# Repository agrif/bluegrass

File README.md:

This is an STM32 board (a la "Blue Pill") with built-in circuitry to charge
a single-cell lithium battery, over USB or DC input. It provides 5V and 3.3V
both at 1A, low standby current, battery fuel gauging, and supports charging
from a solar panel.

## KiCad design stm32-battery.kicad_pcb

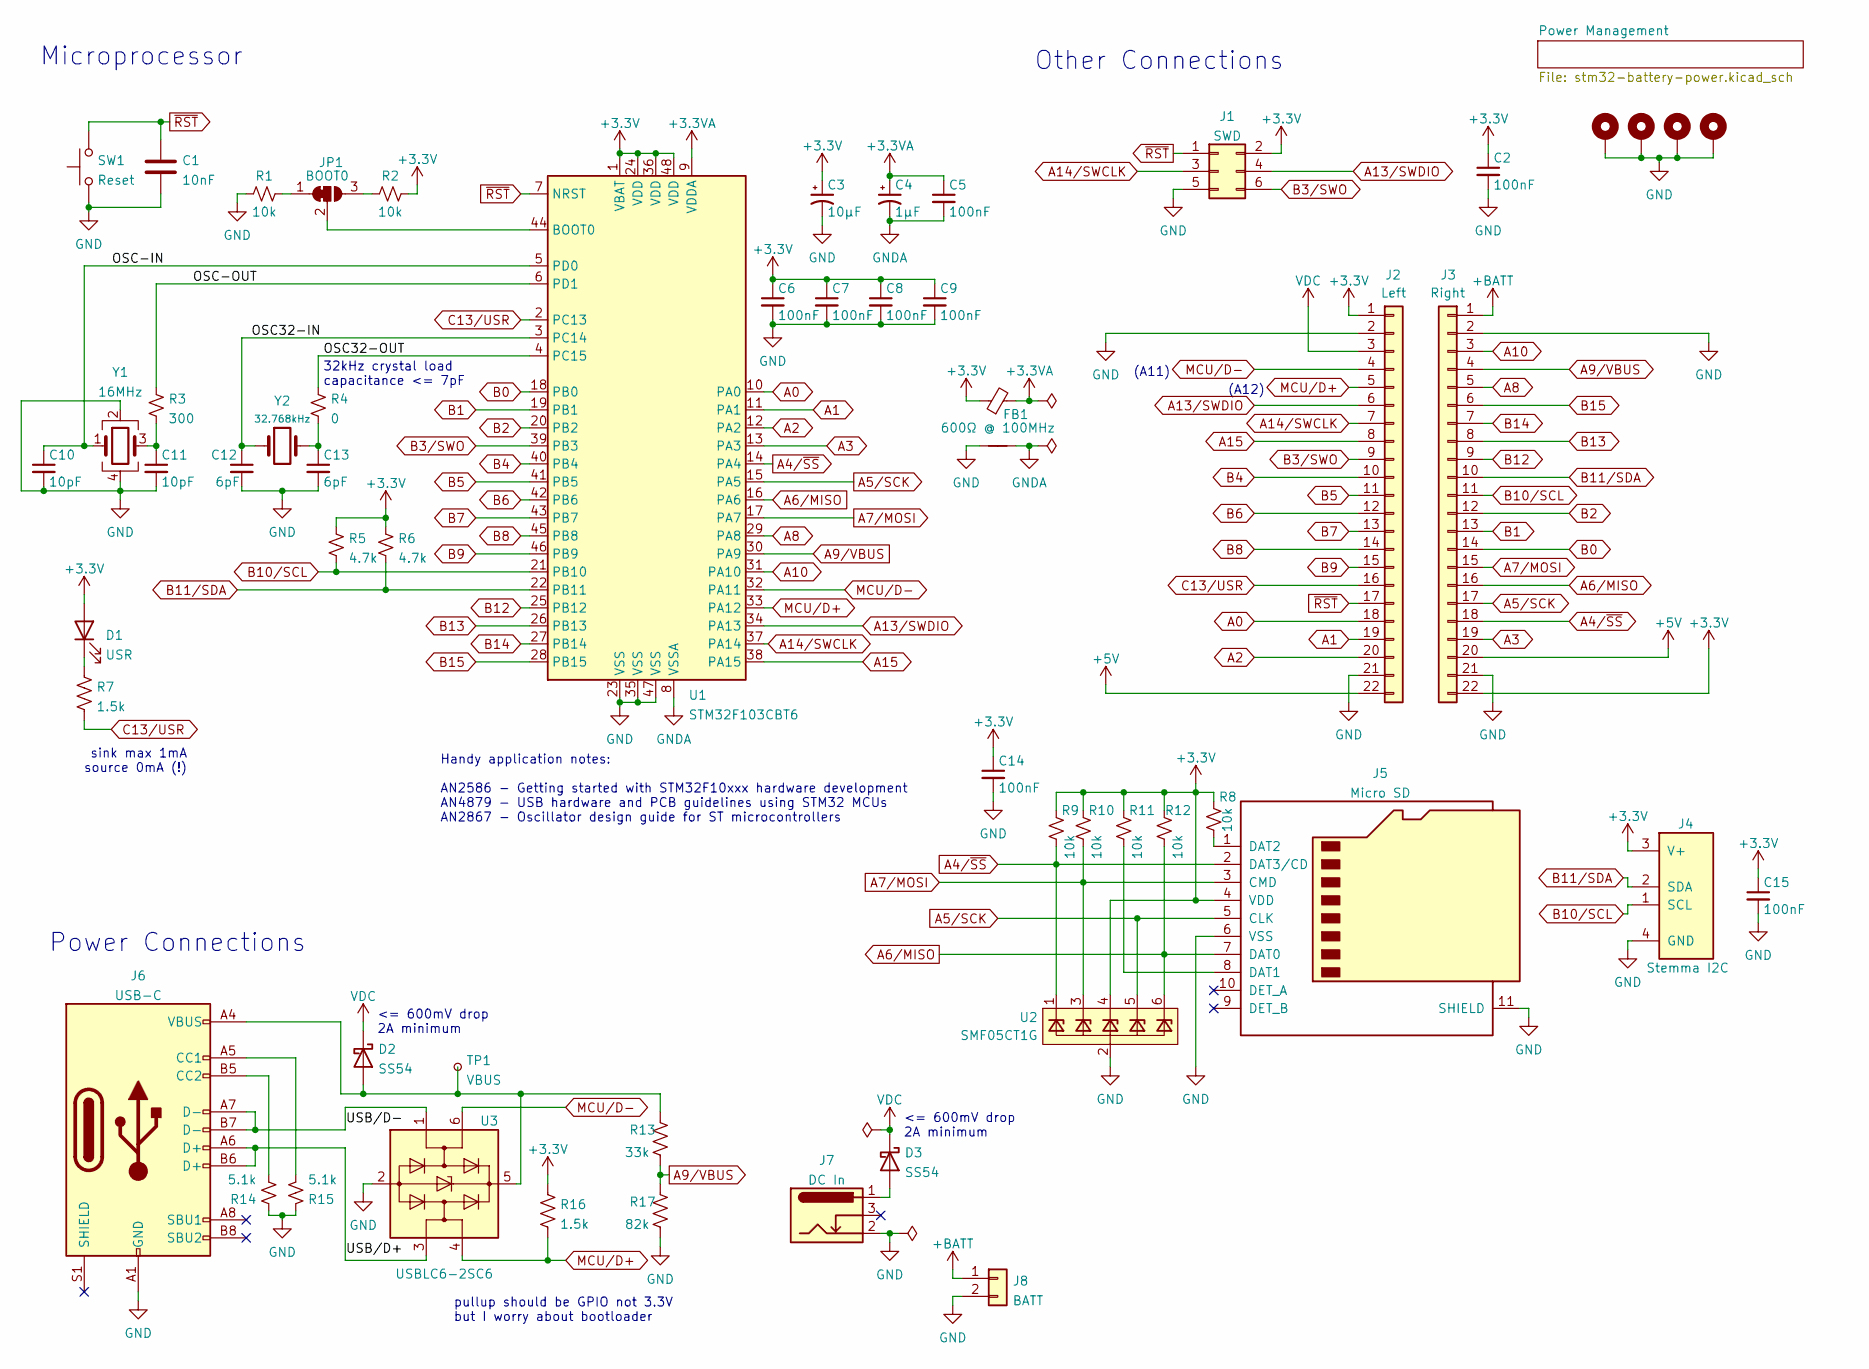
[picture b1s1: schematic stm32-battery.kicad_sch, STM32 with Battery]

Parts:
C1: 10nF; C_0805_2012Metric; LCSC Part # C1710
C2, C5, C6, C7, C8, C9, C14, C15: 100nF; C_0603_1608Metric; LCSC Part # C14663
C3: 10µF; C_0805_2012Metric; LCSC Part # C15850
C4: 1µF; C_0805_2012Metric; LCSC Part # C28323
C10, C11: 10pF; C_0603_1608Metric; LCSC Part # C1634
C12, C13: 6pF; C_0603_1608Metric; LCSC Part # C37474
D1: USR; LED_0805_2012Metric; LCSC Part # C2296
D2, D3: SS54; D_SMA; LCSC Part # C22452
FB1: 600Ω @ 100MHz; L_0805_2012Metric; LCSC Part # C1017
H1, H2, H3, H4: M3; MountingHole_3.2mm_M3_Pad
J1: SWD; PinHeader_2x03_P2.54mm_Vertical
J2: Left; PinHeader_1x22_P2.54mm_Vertical
J3: Right; PinHeader_1x22_P2.54mm_Vertical
J4: Stemma I2C; JST_PH_S4B-PH-K_1x04_P2.00mm_Horizontal
J5: Micro SD; SOFNG-TF-15x15; LCSC Part # C111196
J6: USB-C; USB_C_Receptacle_XKB_U262-16XN-4BVC11; LCSC Part # C319148
J7: DC In; BarrelJack_Horizontal; Digikey # 1939-G-014-4-ND
J8: BATT; JST_PH_S2B-PH-K_1x02_P2.00mm_Horizontal
JP1: BOOT0; SolderJumper-3_P1.3mm_Bridged12_RoundedPad1.0x1.5mm
NT1: NetTie_2; NetTie-2_SMD_Pad2.0mm
R1, R2, R8, R9, R10, R11, R12: 10k; R_0603_1608Metric; LCSC Part # C25804
R3: 300; R_0603_1608Metric; LCSC Part # C23025
R4: 0; R_0603_1608Metric; LCSC Part # C21189
R5, R6: 4.7k; R_0603_1608Metric; LCSC Part # C23162
R7, R16: 1.5k; R_0603_1608Metric; LCSC Part # C22843
R13: 33k; R_0603_1608Metric; LCSC Part # C4216
R14, R15: 5.1k; R_0603_1608Metric; LCSC Part # C23186
R17: 82k; R_0603_1608Metric; LCSC Part # C23254
SW1: Reset; TS-1187A-B-A-B; LCSC Part # C318884
TP1: VBUS; TestPoint_THTPad_D1.0mm_Drill0.5mm
U1: STM32F103CBT6; LQFP-48_7x7mm_P0.5mm; LCSC Part # C8304
U2: SMF05CT1G; SOT-363_SC-70-6; LCSC Part # C15879
U3: USBLC6-2SC6; SOT-23-6; LCSC Part # C2827654
Y1: 16MHz; Crystal_SMD_3225-4Pin_3.2x2.5mm; LCSC Part # C13738
Y2: 32.768kHz; Crystal_SMD_2012-2Pin_2.0x1.2mm; LCSC Part # C97602

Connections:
+3.3VA: C4.1, C5.1, FB1.2, U1.9 (VDDA)
+3V3: C2.1, C3.1, C6.1, C7.1, C8.1, C9.1, C14.1, C15.1, D1.2 (A), FB1.1, J1.2, J2.1, J3.22, J4.3 (V+), J5.4 (VDD), R2.2, R5.1, R6.1, R8.1, R9.1, R10.1, R11.1, R12.1, R16.1, U1.1 (VBAT), U1.24 (VDD), U1.36 (VDD), U1.48 (VDD), U2.4 (K); also elsewhere on the board
+5V: J2.22, J3.20; also elsewhere on the board
+BATT: J3.1, J8.1; also elsewhere on the board
/OSC32-IN: C12.1, U1.3 (PC14), Y2.1
/OSC32-OUT: R4.1, U1.4 (PC15)
/OSC-IN: C10.1, U1.5 (PD0), Y1.1
/OSC-OUT: R3.1, U1.6 (PD1)
/USB/D+: J6.A6 (D+), J6.B6 (D+), U3.3 (I/O2)
/USB/D-: J6.A7 (D-), J6.B7 (D-), U3.1 (I/O1)
A0: J2.18, U1.10 (PA0)
A1: J2.19, U1.11 (PA1)
A2: J2.20, U1.12 (PA2)
A3: J3.19, U1.13 (PA3)
A4/~SS: J3.18, J5.2 (DAT3/CD), R9.2, U1.14 (PA4), U2.1 (K)
A5/SCK: J3.17, J5.5 (CLK), U1.15 (PA5), U2.5 (K)
A6/MISO: J3.16, J5.7 (DAT0), R12.2, U1.16 (PA6), U2.6 (K)
A7/MOSI: J3.15, J5.3 (CMD), R10.2, U1.17 (PA7), U2.3 (K)
A8: J3.5, U1.29 (PA8)
A9/VBUS: J3.4, R13.2, R17.1, U1.30 (PA9)
A10: J3.3, U1.31 (PA10)
A13/SWDIO: J1.4, J2.6, U1.34 (PA13)
A14/SWCLK: J1.3, J2.7, U1.37 (PA14)
A15: J2.8, U1.38 (PA15)
B0: J3.14, U1.18 (PB0)
B1: J3.13, U1.19 (PB1)
B2: J3.12, U1.20 (PB2)
B3/SWO: J1.6, J2.9, U1.39 (PB3)
B4: J2.10, U1.40 (PB4)
B5: J2.11, U1.41 (PB5)
B6: J2.12, U1.42 (PB6)
B7: J2.13, U1.43 (PB7)
B8: J2.14, U1.45 (PB8)
B9: J2.15, U1.46 (PB9)
B10/SCL: J3.11, J4.1 (SCL), R5.2, U1.21 (PB10); also elsewhere on the board
B11/SDA: J3.10, J4.2 (SDA), R6.2, U1.22 (PB11); also elsewhere on the board
B12: J3.9, U1.25 (PB12)
B13: J3.8, U1.26 (PB13)
B14: J3.7, U1.27 (PB14)
B15: J3.6, U1.28 (PB15)
C13/USR: J2.16, R7.2, U1.2 (PC13)
GND: C1.2, C2.2, C3.2, C6.2, C7.2, C8.2, C9.2, C10.2, C11.2, C12.2, C13.2, C14.2, C15.2, H1.1, H2.1, H3.1, H4.1, J1.5, J2.2, J2.21, J3.2, J3.21, J4.4 (GND), J5.6 (VSS), J5.11 (SHIELD), J6.A1 (GND), J6.A12 (GND), J6.B1 (GND), J6.B12 (GND), J7.2, J8.2, NT1.1, R1.1, R14.1, R15.1, R17.2, SW1.1, U1.23 (VSS), U1.35 (VSS), U1.47 (VSS), U2.2 (A), U3.2 (GND), Y1.2, Y1.4; also elsewhere on the board
GNDA: C4.2, C5.2, NT1.2, U1.8 (VSSA)
MCU/D+: J2.5, R16.2, U1.33 (PA12), U3.4 (I/O2)
MCU/D-: J2.4, U1.32 (PA11), U3.6 (I/O1)
unnamed: C11.1, R3.2, Y1.3
unnamed: C13.1, R4.2, Y2.2
unnamed: D1.1 (K), R7.1
unnamed: D2.2 (A), J6.A4 (VBUS), J6.A9 (VBUS), J6.B4 (VBUS), J6.B9 (VBUS), R13.1, TP1.1, U3.5 (VBUS)
unnamed: D3.2 (A), J7.1
unnamed: J5.1 (DAT2), R8.2
unnamed: J5.8 (DAT1), R11.2
unnamed: J6.A5 (CC1), R15.2
unnamed: J6.B5 (CC2), R14.2
unnamed: JP1.1 (A), R1.2
unnamed: JP1.2 (C), U1.44 (BOOT0)
unnamed: JP1.3 (B), R2.1
VDC: D2.1 (K), D3.1 (K), J2.3; also elsewhere on the board
~RST: C1.1, J1.1, J2.17, SW1.2, U1.7 (NRST)

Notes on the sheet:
Power Connections
sink max 1mA source 0mA (!)
pullup should be GPIO not 3.3V but I worry about bootloader
(A12)
Other Connections
32kHz crystal load capacitance <= 7pF
Microprocessor
<= 600mV drop 2A minimum
Handy application notes: AN2586 - Getting started with STM32F10xxx hardware development AN4879 - USB hardware and PCB guidelines using STM32 MCUs AN2867 - Oscillator design guide for ST microcontrollers
(A11)

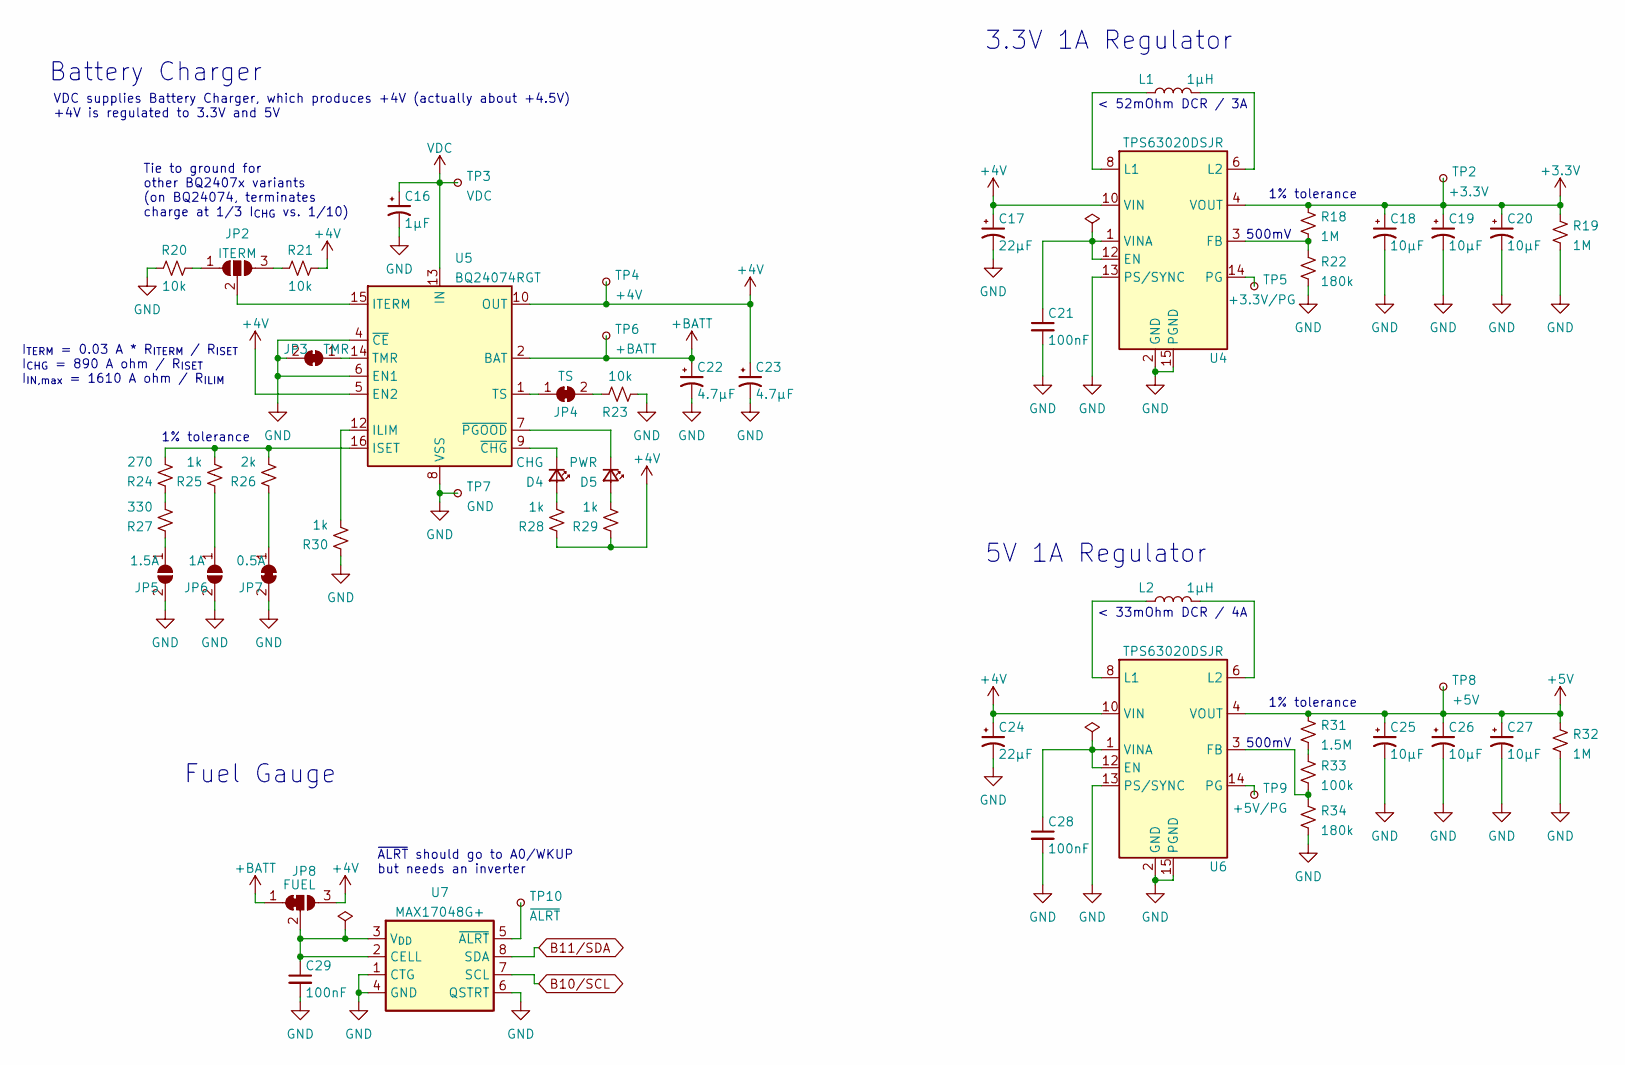
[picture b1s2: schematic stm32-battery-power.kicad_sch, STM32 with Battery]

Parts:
C16: 1µF; C_0805_2012Metric; LCSC Part # C28323
C17, C24: 22µF; C_1206_3216Metric; LCSC Part # C12891
C18, C19, C20, C25, C26, C27: 10µF; C_0805_2012Metric; LCSC Part # C15850
C21, C28, C29: 100nF; C_0603_1608Metric; LCSC Part # C14663
C22, C23: 4.7µF; C_0805_2012Metric; LCSC Part # C1779
D4: CHG; LED_0805_2012Metric; LCSC Part # C84256
D5: PWR; LED_0805_2012Metric; LCSC Part # C2297
JP2: ITERM; SolderJumper-3_P1.3mm_Open_RoundedPad1.0x1.5mm
JP3: TMR; SolderJumper-2_P1.3mm_Bridged_RoundedPad1.0x1.5mm
JP4: TS; SolderJumper-2_P1.3mm_Bridged_RoundedPad1.0x1.5mm
JP5: 1.5A; SolderJumper-2_P1.3mm_Open_RoundedPad1.0x1.5mm
JP6: 1A; SolderJumper-2_P1.3mm_Open_RoundedPad1.0x1.5mm
JP7: 0.5A; SolderJumper-2_P1.3mm_Bridged_RoundedPad1.0x1.5mm
JP8: FUEL; SolderJumper-3_P1.3mm_Bridged12_RoundedPad1.0x1.5mm
L1, L2: 1µH; SWPA6020S; LCSC Part # C98200
R18, R19, R32: 1M; R_0603_1608Metric; LCSC Part # C22935
R20, R21, R23: 10k; R_0603_1608Metric; LCSC Part # C25804
R22, R34: 180k; R_0603_1608Metric; LCSC Part # C22827
R24: 270; R_0603_1608Metric; LCSC Part # C22966
R25, R28, R29, R30: 1k; R_0603_1608Metric; LCSC Part # C21190
R26: 2k; R_0603_1608Metric; LCSC Part # C22975
R27: 330; R_0603_1608Metric; LCSC Part # C23138
R31: 1.5M; R_0603_1608Metric; LCSC Part # C4172
R33: 100k; R_0603_1608Metric; LCSC Part # C25803
TP2: +3.3V; TestPoint_THTPad_D1.0mm_Drill0.5mm
TP3: VDC; TestPoint_THTPad_D1.0mm_Drill0.5mm
TP4: +4V; TestPoint_THTPad_D1.0mm_Drill0.5mm
TP5: +3.3V/PG; TestPoint_THTPad_D1.0mm_Drill0.5mm
TP6: +BATT; TestPoint_THTPad_D1.0mm_Drill0.5mm
TP7: GND; TestPoint_THTPad_1.0x1.0mm_Drill0.5mm
TP8: +5V; TestPoint_THTPad_D1.0mm_Drill0.5mm
TP9: +5V/PG; TestPoint_THTPad_D1.0mm_Drill0.5mm
TP10: ~{ALRT}; TestPoint_THTPad_D1.0mm_Drill0.5mm
U4, U6: TPS63020DSJR; Texas_R-PVSON-N14_ThermalVias; LCSC Part # C15483
U5: BQ24074RGT; VQFN-16-1EP_3x3mm_P0.5mm_EP1.6x1.6mm_ThermalVias; LCSC Part # C54313
U7: MAX17048G+; MAX17048-TDFN-8; LCSC Part # C2682616

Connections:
+3V3: C18.1, C19.1, C20.1, R18.1, R19.1, TP2.1, U4.4 (VOUT), U4.5 (VOUT); also elsewhere on the board
+4V: C17.1, C23.1, C24.1, JP8.3 (B), R21.2, R28.1, R29.1, TP4.1, U4.10 (VIN), U4.11 (VIN), U5.5 (EN2), U5.10 (OUT), U5.11 (OUT), U6.10 (VIN), U6.11 (VIN)
+5V: C25.1, C26.1, C27.1, R31.1, R32.1, TP8.1, U6.4 (VOUT), U6.5 (VOUT); also elsewhere on the board
+BATT: C22.1, JP8.1 (A), TP6.1, U5.2 (BAT), U5.3 (BAT); also elsewhere on the board
B10/SCL: U7.7 (SCL); also elsewhere on the board
B11/SDA: U7.8 (SDA); also elsewhere on the board
GND: C16.2, C17.2, C18.2, C19.2, C20.2, C21.2, C22.2, C23.2, C24.2, C25.2, C26.2, C27.2, C28.2, C29.2, JP3.2 (B), JP5.2 (B), JP6.2 (B), JP7.2 (B), R19.2, R20.1, R22.2, R23.2, R30.1, R32.2, R34.2, TP7.1, U4.2 (GND), U4.13 (PS/SYNC), U4.15 (PGND), U5.4 (~CE), U5.6 (EN1), U5.8 (VSS), U5.17 (VSS), U6.2 (GND), U6.13 (PS/SYNC), U6.15 (PGND), U7.1 (CTG), U7.4 (GND), U7.6 (QSTRT); also elsewhere on the board
unnamed: C21.1, U4.1 (VINA), U4.12 (EN)
unnamed: C28.1, U6.1 (VINA), U6.12 (EN)
unnamed: C29.1, JP8.2 (C), U7.2 (CELL), U7.3 (V_{DD})
unnamed: D4.1 (K), U5.9 (~CHG)
unnamed: D4.2 (A), R28.2
unnamed: D5.1 (K), U5.7 (~PGOOD)
unnamed: D5.2 (A), R29.2
unnamed: JP2.1 (A), R20.2
unnamed: JP2.2 (C), U5.15 (ITERM)
unnamed: JP2.3 (B), R21.1
unnamed: JP3.1 (A), U5.14 (TMR)
unnamed: JP4.1 (A), U5.1 (TS)
unnamed: JP4.2 (B), R23.1
unnamed: JP5.1 (A), R27.1
unnamed: JP6.1 (A), R25.1
unnamed: JP7.1 (A), R26.1
unnamed: L1.1, U4.8 (L1), U4.9 (L1)
unnamed: L1.2, U4.6 (L2), U4.7 (L2)
unnamed: L2.1, U6.8 (L1), U6.9 (L1)
unnamed: L2.2, U6.6 (L2), U6.7 (L2)
unnamed: R18.2, R22.1, U4.3 (FB)
unnamed: R24.1, R27.2
unnamed: R24.2, R25.2, R26.2, U5.16 (ISET)
unnamed: R30.2, U5.12 (ILIM)
unnamed: R31.2, R33.1
unnamed: R33.2, R34.1, U6.3 (FB)
unnamed: TP5.1, U4.14 (PG)
unnamed: TP9.1, U6.14 (PG)
unnamed: TP10.1, U7.5 (~ALRT)
VDC: C16.1, TP3.1, U5.13 (IN); also elsewhere on the board

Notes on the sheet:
Fuel Gauge
1% tolerance
5V 1A Regulator
VDC supplies Battery Charger, which produces +4V (actually about +4.5V) +4V is regulated to 3.3V and 5V
500mV
~{ALRT} should go to A0/WKUP but needs an inverter
< 33mOhm DCR / 4A
< 52mOhm DCR / 3A
I_{TERM} = 0.03 A * R_{ITERM} / R_{ISET} I_{CHG} = 890 A ohm / R_{ISET} I_{IN,max} = 1610 A ohm / R_{ILIM}
Tie to ground for other BQ2407x variants (on BQ24074, terminates charge at 1/3 I_{CHG} vs. 1/10)
3.3V 1A Regulator
Battery Charger

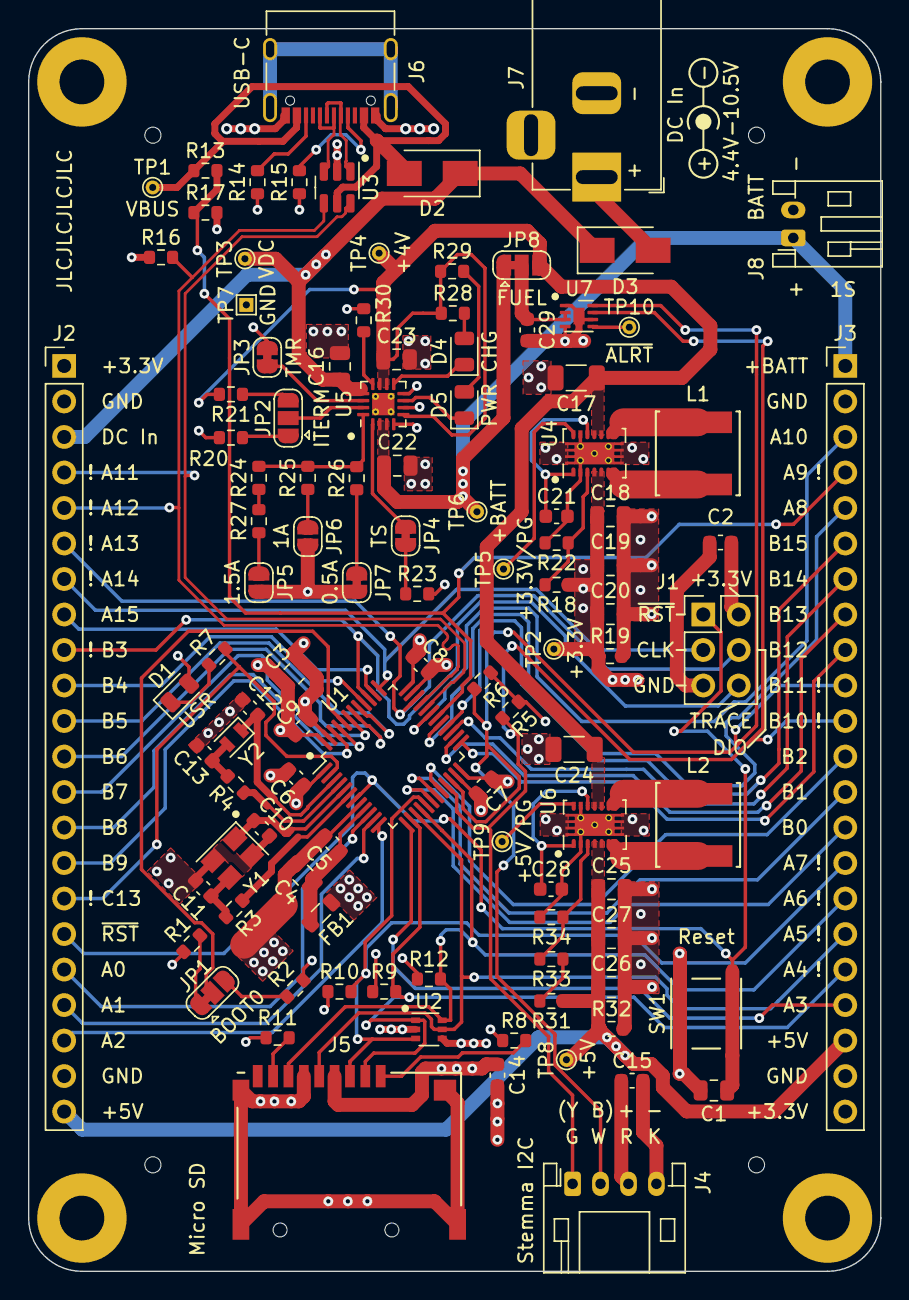
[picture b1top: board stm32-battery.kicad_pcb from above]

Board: 4 copper layers, 61.0 x 88.9 mm, 113 parts (1 on the bottom side), 89 nets.

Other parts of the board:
Ref**: Val**; Rakeri-10mm

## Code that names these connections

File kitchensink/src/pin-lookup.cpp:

#include "kitchensink.h"

struct pin_name_entry {
    const char* name;
    uint32_t pin;
    bool analog_in;
};

static const struct pin_name_entry PIN_NAMES[] = {
    {"D0", D0, false},
    {"D1", D1, false},
    {"D2", D2, false},
    {"D3", D3, false},
    {"D4", D4, false},
    {"D5", D5, false},
    {"D6", D6, false},
    {"D7", D7, false},
    {"D8", D8, false},
    {"D9", D9, false},
    {"D10", D10, false},
    {"D11", D11, false},
    {"D12", D12, false},
    {"D13", D13, false},
    {"D14", D14, false},
    {"D15", D15, false},
    {"D16", D16, false},
    {"D17", D17, false},
    {"D18", D18, false},
    {"D19", D19, false},
    {"D20", D20, false},
    {"D21", D21, false},
    {"D22", D22, false},
    {"D23", D23, false},
    {"D24", D24, false},
    {"D25", D25, false},
    {"D26", D26, false},
    {"D27", D27, false},
    {"D28", D28, false},
    {"D29", D29, false},
    {"D30", D30, false},
    {"D31", D31, false},
    {"D32", D32, false},
    {"D33", D33, false},
    {"D34", D34, false},

    {"A0", A0, true},
    {"A1", A1, true},
    {"A2", A2, true},
    {"A3", A3, true},
    {"A4", A4, true},
    {"A5", A5, true},
    {"A6", A6, true},
    {"A7", A7, true},
    {"A8", A8, true},
    {"A9", A9, true},

    {"PA0", PA0, true},
    {"PA1", PA1, true},
    {"PA2", PA2, true},
    {"PA3", PA3, true},
    {"PA4", PA4, true},
    {"PA5", PA5, true},
    {"PA6", PA6, true},
    {"PA7", PA7, true},
    {"PA8", PA8, false},
    {"PA9", PA9, false},
    {"PA10", PA10, false},
    {"PA11", PA11, false},
    {"PA12", PA12, false},
    {"PA13", PA13, false},
    {"PA14", PA14, false},
    {"PA15", PA15, false},

    {"PB0", PB0, true},
    {"PB1", PB1, true},
    {"PB2", PB2, false},
    {"PB3", PB3, false},
    {"PB4", PB4, false},
    {"PB5", PB5, false},
    {"PB6", PB6, false},
    {"PB7", PB7, false},
    {"PB8", PB8, false},
    {"PB9", PB9, false},
    {"PB10", PB10, false},
    {"PB11", PB11, false},
    {"PB12", PB12, false},
    {"PB13", PB13, false},
    {"PB14", PB14, false},
    {"PB15", PB15, false},

    {"PC13", PC13, false},
    {"PC14", PC14, false},
    {"PC15", PC15, false},

    {"LED_YELLOW", LED_YELLOW, false},
    {"LED_BUILTIN", LED_BUILTIN, false},

    {"PVBUS", PVBUS, false},

    {NULL, 0},
};

uint32_t pin_lookup(const char* name, uint32_t* pin, bool analog_in) {
    if (isdigit(name[0]) && strlen(name) <= 2) {
        // try to interpret this as either D## or A##
        char new_name[4];
        if (analog_in) {
            new_name[0] = 'A';
        } else {
            new_name[0] = 'D';
        }

        new_name[1] = name[0];
        new_name[2] = name[1];
        new_name[3] = 0;

        if (pin_lookup(new_name, pin, analog_in)) {
            return true;
        }
    }

    for (int i = 0; PIN_NAMES[i].name != NULL; i++) {
        if (analog_in && !PIN_NAMES[i].analog_in) {
            continue;
        }

        if (strcasecmp(PIN_NAMES[i].name, name) == 0) {
            *pin = PIN_NAMES[i].pin;
            return true;
        }
    }

    return false;
}

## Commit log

2022-09-16 jlcpcb order #, tooling, export
2022-09-28 part numbers for jst connectors / dc barrel jac
2022-10-03 move kicad stuff into subdirectory, new name
2022-10-03 blink example
2022-10-03 added bootloader
2022-10-15 added a kitchen sink project
2022-10-15 added coremark to kitchen sink
2022-10-15 kitchensink: more better english, wait on serial connect
2022-10-15 kitchensink: better \r \n handling
2022-10-15 kitchensink: use \r\n line endings
2022-10-15 kitchensink: add url to banner
2022-10-15 blink: use cpp not c (since most people will use cpp)
2022-10-15 kitchensink: use pulldown on vbus pin
2022-11-25 battery-logger: added a low-power logging example
2022-11-26 kitchensink: add analog input
2022-11-26 kitchensink: add a note about LSE/RTC failure
2022-11-26 kitchensink: add coremark test
2022-11-27 kitchensink: morse code led
2022-11-27 kitchensink: sd card read/write speed test
2022-11-27 kitchensink: ignore unhandled non-printable input
2022-11-27 kitchensink: line editing
2022-11-27 kitchensink: history
2022-11-27 kitchensink: move interact stuff to separate header
2022-11-27 kitchensink: quiet a warning about extern "C"
2022-11-27 kitchensink: print id number in banner
2022-11-27 kitchensink: changes to make putty happy
2022-11-27 kitchensink: shenanigans
2022-11-27 kitchensink: smaller code means different coremark score
2022-11-29 kitchensink: gpio read/write
2022-11-29 kitchensink: add git hash to version banner
2022-11-29 kitchensink: low power sleeps
2022-11-29 kitchensink: manage compile flags better
2022-11-30 kitchensink: break out version command
2022-11-30 battery-logger: temperature and morse heartbeat
2022-11-30 battery-logger: use delay not sleep in morse
2022-12-18 logo: added rev.1 logo
2022-12-18 logo: logo should really go in README
2022-12-18 logo: added an info card
2022-12-20 logo: card should have baud
2025-01-22 rust blink / serial CDC example
